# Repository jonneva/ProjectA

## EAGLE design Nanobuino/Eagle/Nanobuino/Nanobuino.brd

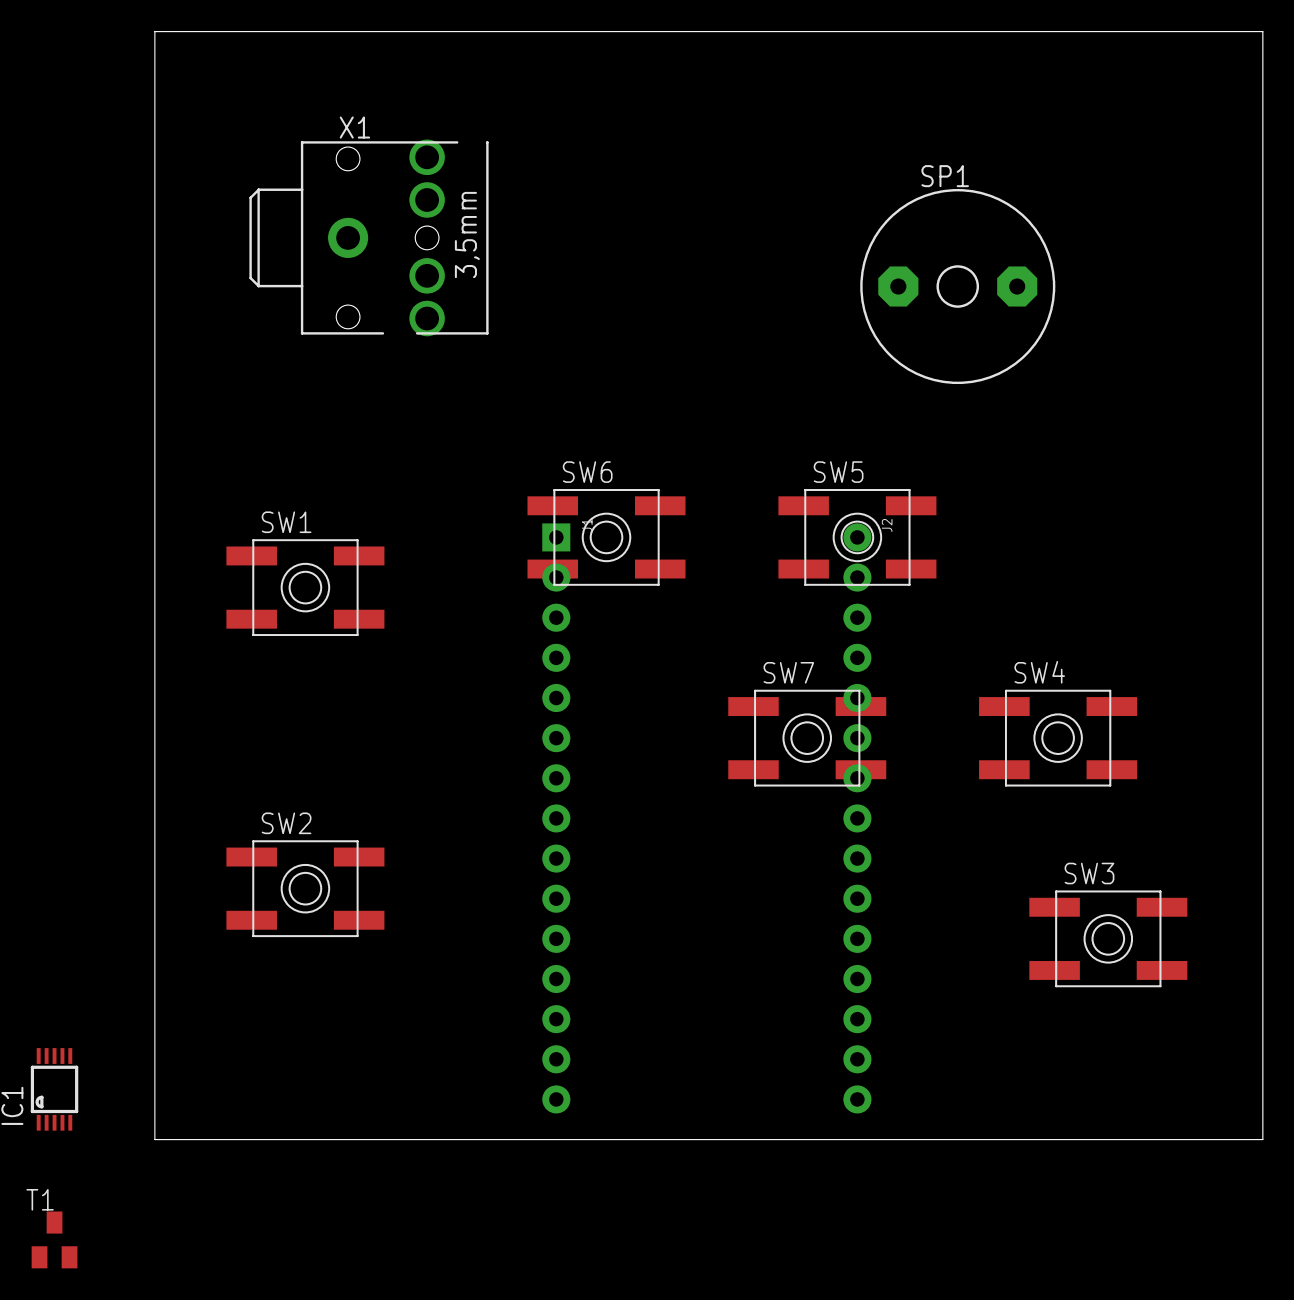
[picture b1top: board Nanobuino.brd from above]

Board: 2 copper layers, 70.1 x 70.1 mm, 13 parts (0 on the bottom side), 2 nets, no tracks yet.

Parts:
IC1: MCP73833-UN; MSOP10
J1: HEAD15-NOSS
J2: HEAD15-NOSS-1
SP1: SPEAKER/AL60P; AL60P
SW1, SW2, SW3, SW4, SW5, SW6, SW7: SPST_TACT-EVQQ2; EVQ-Q2
T1: SOT23-BEC
X1: STEREOJACK; STX3100

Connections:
COM: J1.4, J2.2
RESET: J1.3, J2.3

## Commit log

2014-08-13 Initial commit, just Arduino Uno ref board
2014-08-14 Fritzing & pics added
2014-08-14 Added usefull stuff
2014-08-15 Nanobuino Eagle layout started
2014-08-15 Background info for design
2014-08-15 clean
2014-08-15 Lots of parts added to schematic
2014-08-16 1st layout
